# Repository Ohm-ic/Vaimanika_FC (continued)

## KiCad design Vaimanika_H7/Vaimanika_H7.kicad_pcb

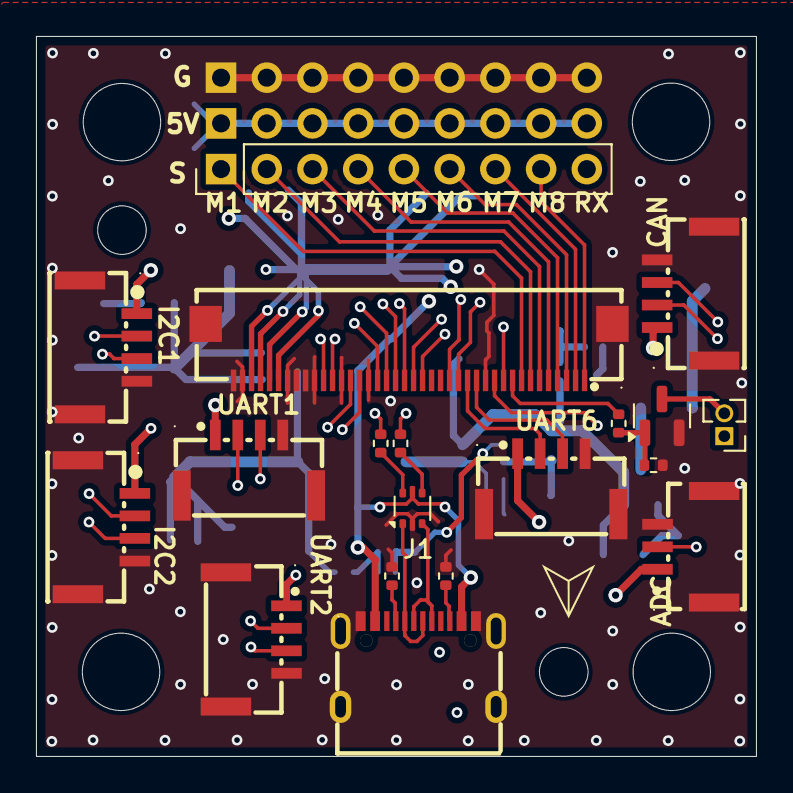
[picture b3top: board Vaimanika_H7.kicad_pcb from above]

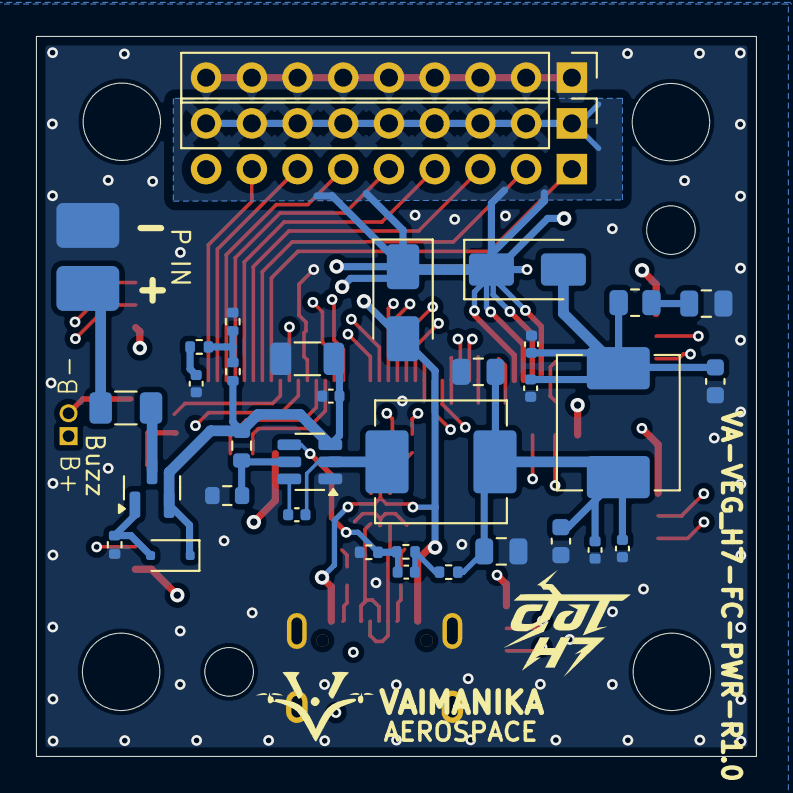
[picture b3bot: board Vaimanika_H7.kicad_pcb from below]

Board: 4 copper layers, 40.0 x 40.0 mm, 61 parts (36 on the bottom side), 50 nets.

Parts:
C2: 10uF; C_1206_3216Metric
C3, C16, C20: 100nF; C_0402_1005Metric
C5, C7: 0.1uF; C_0402_1005Metric
C9, C11: 22uF; C_0805_2012Metric
C12, C18: 4.7uF; C_0603_1608Metric
C14: 75pF; C_0402_1005Metric
C15, C19: 1uF; C_0402_1005Metric
C17: 47uF; C_0805_2012Metric
CN1: WAFER-GH1.25-3PWB; CONN-TH_3P-P1.25_GH1.25
D1, D2: SS34; D_SMA
D3: MM3Z10VT1G; D_SOD-323F
F1: CFS12V3T5R0; Fuse_1206_3216Metric
FPC1: AFC24-S40FIA-HF; FPC-SMD_40P-P0.50_AFC24-S40FIA-HF
H1, H2, H3, H4: MountingHole; MountingHole_4.3mm_M4
H5: MountingHole; MountingHole_2.7mm_M2.5_DIN965
H6: MountingHole; MountingHole_2.7mm_M2.5
J1: TYPE-C 16PIN 2MD; USB-C-SMD_TYPE-C-16PIN-2MD-073
J2, J3, J6: Conn_01x09; PinHeader_1x09_P2.54mm_Vertical
J4: +VLIPO; SolderPads_1x1_2.5_3.5
J5: GND; SolderPads_1x1_2.5_3.5
J8: Conn_01x02; PinHeader_1x02_P1.27mm_Vertical
L2: 10uH; L_TechFuse_SL0630
L3: 10uH; L_Chilisin_BMRB00060612
Q1: AO3400A; SOT-23
Q2: AO3401A; SOT-23
R1: 18K; R_0402_1005Metric
R2: 2K; R_0402_1005Metric
R3, R4: 100; R_0402_1005Metric
R5: 10K; R_0402_1005Metric
R8: 511K; R_0603_1608Metric
R9: 105K; R_0603_1608Metric
R10, R11: 22; R_0402_1005Metric
R12, R13: 5.1K; R_0402_1005Metric
R17: 49.9; R_0402_1005Metric
R18, R21: 100K; R_0402_1005Metric
R19: 13.3K; R_0402_1005Metric
R20: 1; R_0805_2012Metric
U2: TPS54302; SOT-23-6
U3: USBLC6-2P6; SOT-666
U4, U5, U6: WAFER-GH1.25-4PWB; CONN-SMD_4P-P1.25_XUNPU_WAFER-GH1.25-4PWB
U7, U8, U9: WAFER-GH1.25-4PLB; CONN-SMD_4P-P1.25_XUNPU_WAFER-GH1.25-4PLB

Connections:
+5VBAT: C9.1, C11.1, C12.1, C15.1, C16.1, L2.2, L3.1, R17.2
+5VBUS: D2.2 (A), J1.A4B9 (VBUS), J1.B4A9 (VBUS), U3.5 (VBUS)
+5VFIL: C18.1, C19.1, C20.1, D1.2 (A), L3.2, R20.2
+VIN: C2.1, C5.1, D3.1 (K), Q2.2 (S), R1.1, R8.2, U2.3 (VIN)
+VLIPO: F1.1, J4.1
ADC: CN1.2, FPC1.11
ADC_VOLTAGE: C3.1, R4.2
BUZZER: FPC1.9, R3.1
CAN_H: FPC1.27, U6.2
CAN_L: FPC1.26, U6.3
GND: C2.2, C3.2, C5.2, C9.2, C11.2, C12.2, C15.2, C16.2, C17.2, C18.2, C19.2, C20.2, CN1.3, CN1.4, CN1.5, FPC1.12, FPC1.25, FPC1.28, FPC1.31, FPC1.32, FPC1.33, FPC1.34, FPC1.39, FPC1.40, FPC1.41, FPC1.42, J1.13 (EH), J1.14 (EH), J1.A1B12 (GND), J1.B1A12 (GND), J3.1, J3.2, J3.3, J3.4, J3.5, J3.6, J3.7, J3.8, J3.9, J5.1, Q1.2 (S), R2.2, R5.2, R9.1, R12.1, R13.1, R19.1, R21.2, U2.1 (GND), U3.2 (GND), U4.4, U4.5, U4.6, U5.4, U5.5, U5.6, U6.4, U6.5, U6.6, U7.4, U7.5, U7.6, U8.4, U8.5, U8.6, U9.4, U9.5, U9.6
I2C2_SCL: FPC1.22, U5.2
I2C2_SDA: FPC1.21, U5.3
MOTOR1: FPC1.8, J6.1
MOTOR2: FPC1.7, J6.2
MOTOR3: FPC1.6, J6.3
MOTOR4: FPC1.5, J6.4
MOTOR5: FPC1.4, J6.5
MOTOR6: FPC1.3, J6.6
MOTOR7: FPC1.2, J6.7
MOTOR8: FPC1.1, J6.8
unnamed: C14.1, R17.1, R18.2
unnamed: C17.1, R20.1
unnamed: D3.2 (A), Q2.1 (G), R21.1
unnamed: J1.A5 (CC1), R12.2
unnamed: J1.B5 (CC2), R13.2
unnamed: Q1.1 (G), R3.2, R5.1
unnamed: F1.2, Q2.3 (D)
unnamed: R1.2, R2.1, R4.1
unnamed: R10.1, U3.6 (I/O1)
unnamed: R11.1, U3.4 (I/O2)
unnamed: C7.1, U2.6 (BOOT)
unnamed: R8.1, R9.2, U2.5 (EN)
unnamed: C14.2, R18.1, R19.2, U2.4 (FB)
unnamed: C7.2, L2.1, U2.2 (SW)
PIN_B+: CN1.1, D1.1 (K), D2.1 (K), FPC1.35, FPC1.36, FPC1.37, FPC1.38, J2.1, J2.2, J2.3, J2.4, J2.5, J2.6, J2.7, J2.8, J2.9, J8.1, U4.1, U5.1, U6.1, U7.1, U8.1, U9.1
PIN_B-: J8.2, Q1.3 (D)
RX_PPM: FPC1.10, J6.9
SCL_BARO: FPC1.23, U4.2
SDA_BARO: FPC1.24, U4.3
UART2_RX: FPC1.15, U8.3
UART2_TX: FPC1.16, U8.2
USART1_RX: FPC1.19, U9.3
USART1_TX: FPC1.20, U9.2
USART6_RX: FPC1.13, U7.3
USART6_TX: FPC1.14, U7.2
USB_CON_D+: J1.A6 (Dp1), J1.B6 (Dp2), U3.3 (I/O2)
USB_CON_D-: J1.A7 (Dn1), J1.B7 (Dn2), U3.1 (I/O1)
USB_D+: FPC1.30, R11.2
USB_D-: FPC1.29, R10.2

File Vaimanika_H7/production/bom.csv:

Designator,Footprint,Quantity,Value,LCSC Part #
"C11, C9",0805,2,22uF,C6119899
"C12, C18",0603,2,4.7uF,C19666
C14,0402,1,75pF,C107010
"C15, C19",0402,2,1uF,C14445
"C16, C20, C3",0402,3,100nF,C60474
C17,0805,1,47uF,C16780
C2,1206,1,10uF,C7432781
"C5, C7",0402,2,0.1uF,C152814
CN1,CONN-TH_3P-P1.25_GH1.25,1,WAFER-GH1.25-3PWB,C3029378
"D1, D2",D_SMA,2,SS34,C8678
D3,D_SOD-323F,1,MM3Z10VT1G,C39057
F1,1206,1,CFS12V3T5R0,C163128
FPC1,FPC-SMD_40P-P0.50_AFC24-S40FIA-HF,1,AFC24-S40FIA-HF,C49260550
J1,USB-C-SMD_TYPE-C-16PIN-2MD-073,1,TYPE-C 16PIN 2MD,C2765186
"J2, J3, J6",PinHeader_1x09_P2.54mm_Vertical,3,Conn_01x09,
J4,SolderPads_1x1_2.5_3.5,1,+VLIPO,
J5,SolderPads_1x1_2.5_3.5,1,GND,
J8,PinHeader_1x02_P1.27mm_Vertical,1,Conn_01x02,
L2,L_TechFuse_SL0630,1,10uH,C917354
L3,L_Chilisin_BMRB00060612,1,10uH,C128692
Q1,SOT-23,1,AO3400A,C20917
Q2,SOT-23,1,AO3401A,C15127
R1,0402,1,18K,C25762
"R10, R11",0402,2,22,C114765
"R12, R13",0402,2,5.1K,C25905
R17,0402,1,49.9,C87044
"R18, R21",0402,2,100K,C60491
R19,0402,1,13.3K,C2974007
R2,0402,1,2K,C4109
R20,0805,1,1,C2907233
"R3, R4",0402,2,100,C106232
R5,0402,1,10K,C25744
R8,0603,1,511K,C2930114
R9,0603,1,105K,C2933128
U2,SOT-23-6,1,TPS54302,C311983
U3,SOT-666,1,USBLC6-2P6,C15999
"U4, U5, U6",CONN-SMD_4P-P1.25_XUNPU_WAFER-GH1.25-4PWB,3,WAFER-GH1.25-4PWB,C3029379
"U7, U8, U9",CONN-SMD_4P-P1.25_XUNPU_WAFER-GH1.25-4PLB,3,WAFER-GH1.25-4PLB,C3029370

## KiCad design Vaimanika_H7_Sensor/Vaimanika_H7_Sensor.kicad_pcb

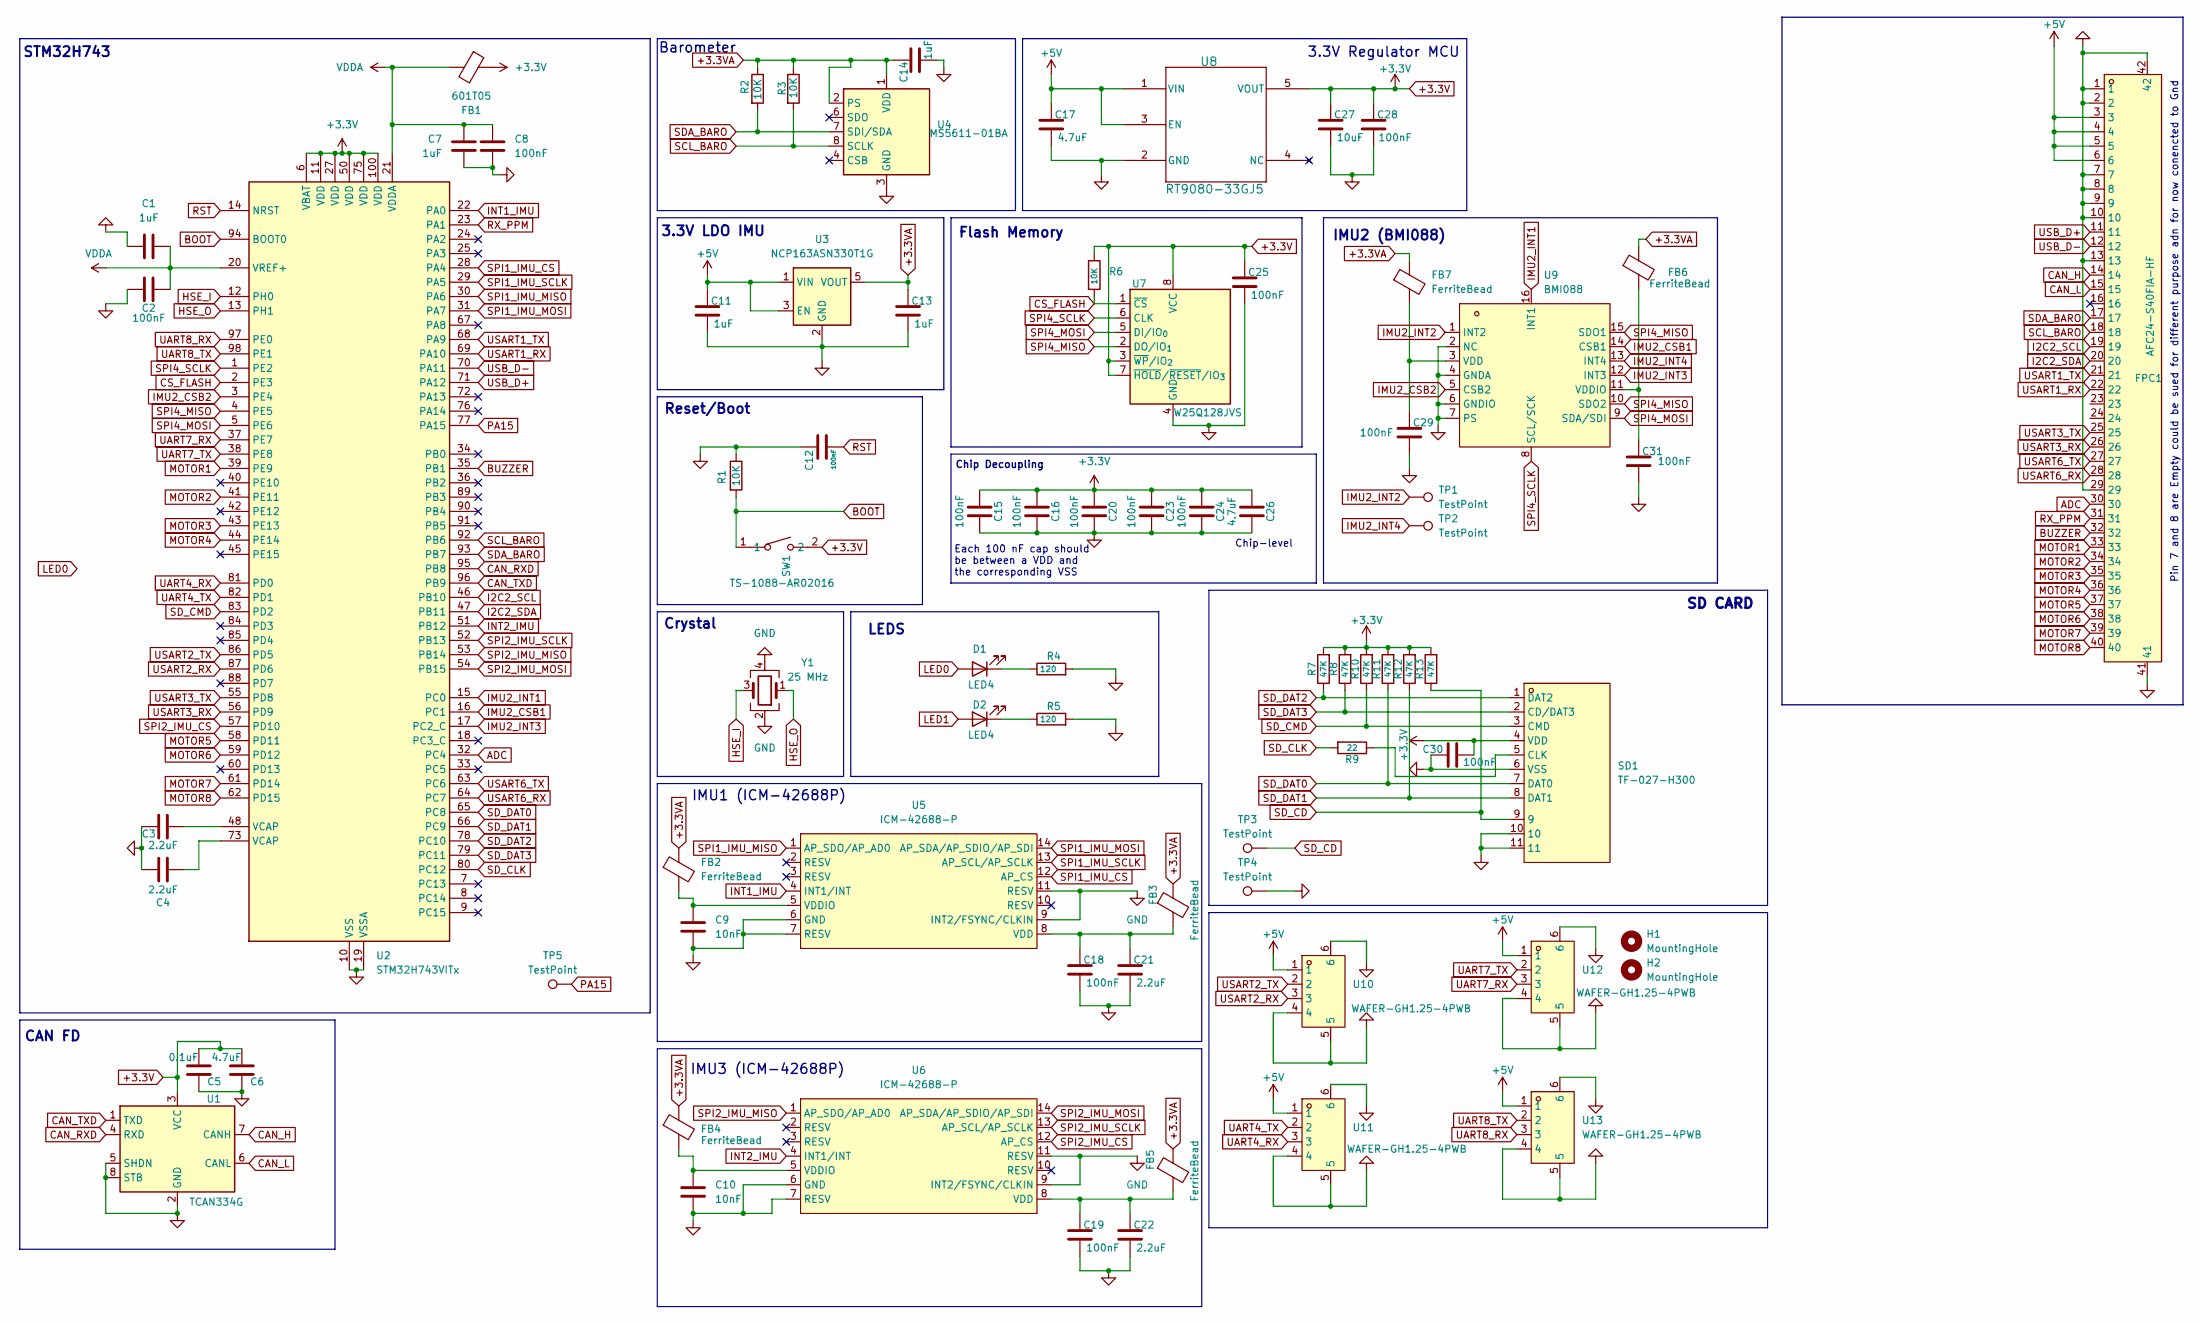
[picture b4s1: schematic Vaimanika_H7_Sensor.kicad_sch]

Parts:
C1, C7, C11, C13, C14: 1uF; C_0402_1005Metric; LCSC C380294
C2, C8, C12, C15, C16, C18, C19, C20, C23, C24, C25, C28, C29, C30, C31: 100nF; C_0402_1005Metric; LCSC C60474
C3, C4, C21, C22: 2.2uF; C_0402_1005Metric; LCSC C53032641
C5: 0.1uF; C_0402_1005Metric; LCSC C152814
C6, C17, C26: 4.7uF; C_0402_1005Metric; LCSC C6119782
C9, C10: 10nF; C_0402_1005Metric; LCSC C6119808
C27: 10uF; C_0402_1005Metric; LCSC C15525
D1, D2: LED4; LED_0402_1005Metric; LCSC C965793
FB1: 601T05; L_0603_1608Metric; LCSC C133937
FB2, FB3, FB4, FB5, FB6, FB7: FerriteBead; L_0402_1005Metric; LCSC C76884
FPC1: AFC24-S40FIA-HF; FPC-SMD_40P-P0.50_AFC24-S40FIA-HF; MPN AFC24-S40FIA-HF; LCSC Part C49260550
H1, H2: MountingHole; MountingHole_2.7mm_M2.5_DIN965
R1, R6: 10K; R_0402_1005Metric; LCSC C25744
R2, R3: 10K; C_0402_1005Metric; LCSC C25744
R4, R5: 120; R_0402_1005Metric; LCSC C25079
R7, R8, R10, R11, R12, R13: 47K; R_0402_1005Metric; LCSC C25133
R9: 22; R_0402_1005Metric; LCSC C114765
SD1: TF-027-H300; TF-SMD_HYCW104-TF08-375B; LCSC Part C5310495
SW1: TS-1088-AR02016; SW-SMD_L3.9-W3.0-P4.45; LCSC C720477
TP1, TP2, TP3, TP4, TP5: TestPoint; TestPoint_Pad_D1.0mm
U1: TCAN334G; SOT-23-8; LCSC C191005
U2: STM32H743VITx; LQFP-100_14x14mm_P0.5mm; LCSC C114409
U3: NCP163ASN330T1G; SOT-23-5; LCSC C892187
U4: MS5611-01BA; LGA-8_3x5mm_P1.25mm; LCSC C15639
U5, U6: ICM-42688-P; LGA-14_L3.0-W2.5-P0.50-TL; LCSC Part C1850418
U7: W25Q128JVS; SOIC-8_L5.3-W5.3-P1.27-LS8.0-BL; LCSC C97521
U8: RT9080-33GJ5; TSOT-23-5; LCSC C841192
U9: BMI088; LGA-16_L4.5-W3.0-P0.50-BL; LCSC Part C194919
U10, U11, U12, U13: WAFER-GH1.25-4PWB; CONN-SMD_4P-P1.25_XUNPU_WAFER-GH1.25-4PWB; MPN WAFER-GH1.25-4PWB; LCSC C3029379
Y1: 25 MHz; CRYSTAL-SMD_4P-L3.2-W2.5-BL; LCSC C3034302

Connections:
+3.3V: C5.2, C6.2, C15.1, C16.1, C20.1, C23.1, C24.1, C25.1, C26.1, C27.1, C28.1, C30.2, FB1.1, R6.1, R7.2, R8.2, R10.2, R11.2, R12.2, R13.2, SD1.4 (VDD), SW1.2, U1.3 (VCC), U2.6 (VBAT), U2.11 (VDD), U2.27 (VDD), U2.50 (VDD), U2.75 (VDD), U2.100 (VDD), U7.3 (~WP/IO_{2}), U7.7 (~HOLD/~RESET/IO_{3}), U7.8 (VCC), U8.5 (VOUT)
+3.3VA: C13.1, C14.1, FB2.1, FB3.1, FB4.1, FB5.1, FB6.1, FB7.1, R2.1, R3.1, U3.5 (VOUT), U4.1 (VDD), U4.2 (PS)
+5V: C11.1, C17.1, FPC1.3, FPC1.4, FPC1.5, FPC1.6, U3.1 (VIN), U3.3 (EN), U8.1 (VIN), U8.3 (EN), U10.1, U11.1, U12.1, U13.1
ADC: FPC1.30, U2.32 (PC4)
BOOT: R1.2, SW1.1, U2.94 (BOOT0)
BUZZER: FPC1.32, U2.35 (PB1)
CAN_H: FPC1.14, U1.7 (CANH)
CAN_L: FPC1.15, U1.6 (CANL)
CAN_RXD: U1.4 (RXD), U2.95 (PB8)
CAN_TXD: U1.1 (TXD), U2.96 (PB9)
CS_FLASH: R6.2, U2.2 (PE3), U7.1 (~CS)
GND: C1.1, C2.1, C3.1, C4.1, C5.1, C6.1, C7.2, C8.2, C9.2, C10.2, C11.2, C12.1, C13.2, C14.2, C15.2, C16.2, C17.2, C18.2, C19.2, C20.2, C21.2, C22.2, C23.2, C24.2, C25.2, C26.2, C27.2, C28.2, C29.2, C30.1, C31.2, FPC1.1, FPC1.2, FPC1.7, FPC1.8, FPC1.9, FPC1.10, FPC1.13, FPC1.29, FPC1.41, FPC1.42, R1.1, R4.2, R5.2, SD1.6 (VSS), SD1.10, SD1.11, TP4.1, U1.2 (GND), U1.5 (SHDN), U1.8 (STB), U2.10 (VSS), U2.19 (VSSA), U2.26 (VSS), U2.49 (VSS), U2.74 (VSS), U2.99 (VSS), U3.2 (GND), U4.3 (GND), U5.6 (GND), U5.7 (RESV), U5.9 (INT2/FSYNC/CLKIN), U5.11 (RESV), U6.6 (GND), U6.7 (RESV), U6.9 (INT2/FSYNC/CLKIN), U6.11 (RESV), U7.4 (GND), U8.2 (GND), U9.2 (NC), U9.4 (GNDA), U9.6 (GNDIO), U9.7 (PS), U10.4, U10.5, U10.6, U11.4, U11.5, U11.6, U12.4, U12.5, U12.6, U13.4, U13.5, U13.6, Y1.2, Y1.4
HSE_I: U2.12 (PH0), Y1.3
HSE_O: U2.13 (PH1), Y1.1
I2C2_SCL: FPC1.19, U2.46 (PB10)
I2C2_SDA: FPC1.20, U2.47 (PB11)
IMU2_CSB1: U2.16 (PC1), U9.14 (CSB1)
IMU2_CSB2: U2.3 (PE4), U9.5 (CSB2)
IMU2_INT1: U2.15 (PC0), U9.16 (INT1)
IMU2_INT2: TP1.1, U9.1 (INT2)
IMU2_INT3: U2.17 (PC2_C), U9.12 (INT3)
IMU2_INT4: TP2.1, U9.13 (INT4)
INT1_IMU: U2.22 (PA0), U5.4 (INT1/INT)
INT2_IMU: U2.51 (PB12), U6.4 (INT1/INT)
LED0: D1.2 (A)
LED1: D2.2 (A)
MOTOR1: FPC1.33, U2.39 (PE9)
MOTOR2: FPC1.34, U2.41 (PE11)
MOTOR3: FPC1.35, U2.43 (PE13)
MOTOR4: FPC1.36, U2.44 (PE14)
MOTOR5: FPC1.37, U2.58 (PD11)
MOTOR6: FPC1.38, U2.59 (PD12)
MOTOR7: FPC1.39, U2.61 (PD14)
MOTOR8: FPC1.40, U2.62 (PD15)
unnamed: C3.2, U2.48 (VCAP)
unnamed: C4.2, U2.73 (VCAP)
unnamed: D1.1 (K), R4.1
unnamed: D2.1 (K), R5.1
unnamed: R9.1, SD1.5 (CLK)
unnamed: C18.1, C21.1, FB3.2, U5.8 (VDD)
unnamed: C9.1, FB2.2, U5.5 (VDDIO)
unnamed: C19.1, C22.1, FB5.2, U6.8 (VDD)
unnamed: C10.1, FB4.2, U6.5 (VDDIO)
unnamed: C29.1, FB7.2, U9.3 (VDD)
unnamed: C31.1, FB6.2, U9.11 (VDDIO)
PA15: TP5.1, U2.77 (PA15)
RST: C12.2, U2.14 (NRST)
RX_PPM: FPC1.31, U2.23 (PA1)
SCL_BARO: FPC1.18, R3.2, U2.92 (PB6), U4.8 (SCLK)
SDA_BARO: FPC1.17, R2.2, U2.93 (PB7), U4.7 (SDI/SDA)
SD_CD: R13.1, SD1.9, TP3.1
SD_CLK: R9.2, U2.80 (PC12)
SD_CMD: R10.1, SD1.3 (CMD), U2.83 (PD2)
SD_DAT0: R11.1, SD1.7 (DAT0), U2.65 (PC8)
SD_DAT1: R12.1, SD1.8 (DAT1), U2.66 (PC9)
SD_DAT2: R7.1, SD1.1 (DAT2), U2.78 (PC10)
SD_DAT3: R8.1, SD1.2 (CD/DAT3), U2.79 (PC11)
SPI1_IMU_CS: U2.28 (PA4), U5.12 (AP_CS)
SPI1_IMU_MISO: U2.30 (PA6), U5.1 (AP_SDO/AP_AD0)
SPI1_IMU_MOSI: U2.31 (PA7), U5.14 (AP_SDA/AP_SDIO/AP_SDI)
SPI1_IMU_SCLK: U2.29 (PA5), U5.13 (AP_SCL/AP_SCLK)
SPI2_IMU_CS: U2.57 (PD10), U6.12 (AP_CS)
SPI2_IMU_MISO: U2.53 (PB14), U6.1 (AP_SDO/AP_AD0)
SPI2_IMU_MOSI: U2.54 (PB15), U6.14 (AP_SDA/AP_SDIO/AP_SDI)
SPI2_IMU_SCLK: U2.52 (PB13), U6.13 (AP_SCL/AP_SCLK)
SPI4_MISO: U2.4 (PE5), U7.2 (DO/IO_{1}), U9.10 (SDO2), U9.15 (SDO1)
SPI4_MOSI: U2.5 (PE6), U7.5 (DI/IO_{0}), U9.9 (SDA/SDI)
SPI4_SCLK: U2.1 (PE2), U7.6 (CLK), U9.8 (SCL/SCK)
UART4_RX: U2.81 (PD0), U11.3
UART4_TX: U2.82 (PD1), U11.2
UART7_RX: U2.37 (PE7), U12.3
UART7_TX: U2.38 (PE8), U12.2
UART8_RX: U2.97 (PE0), U13.3
UART8_TX: U2.98 (PE1), U13.2
USART1_RX: FPC1.22, U2.69 (PA10)
USART1_TX: FPC1.21, U2.68 (PA9)
USART2_RX: U2.87 (PD6), U10.3
USART2_TX: U2.86 (PD5), U10.2
USART3_RX: FPC1.26, U2.56 (PD9)
USART3_TX: FPC1.25, U2.55 (PD8)
USART6_RX: FPC1.28, U2.64 (PC7)
USART6_TX: FPC1.27, U2.63 (PC6)
USB_D+: FPC1.11, U2.71 (PA12)
USB_D-: FPC1.12, U2.70 (PA11)
VDDA: C1.2, C2.2, C7.1, C8.1, FB1.2, U2.20 (VREF+), U2.21 (VDDA)

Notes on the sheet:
CAN FD
Flash Memory
Chip Decoupling
SD CARD
LEDS
Crystal
3.3V LDO IMU
Each 100 nF cap should be between a VDD and the corresponding VSS
Barometer
3.3V Regulator MCU
Pin 7 and 8 are Empty could be sued for different purpose adn for now conencted to Gnd
IMU1 (ICM-42688P)
IMU2 (BMI088)
STM32H743
IMU3 (ICM-42688P)
Reset/Boot
Chip-level

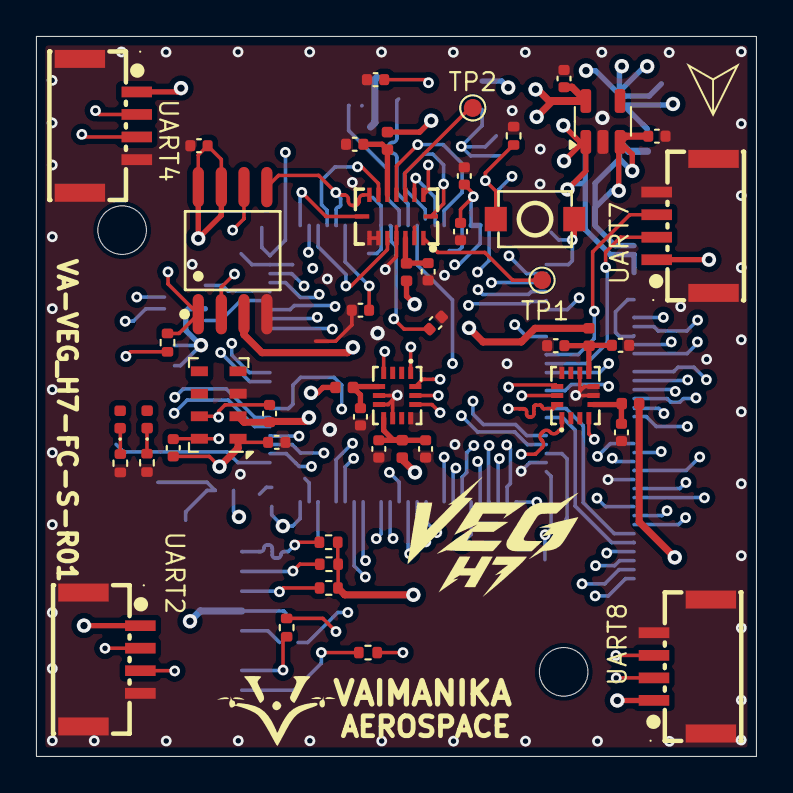
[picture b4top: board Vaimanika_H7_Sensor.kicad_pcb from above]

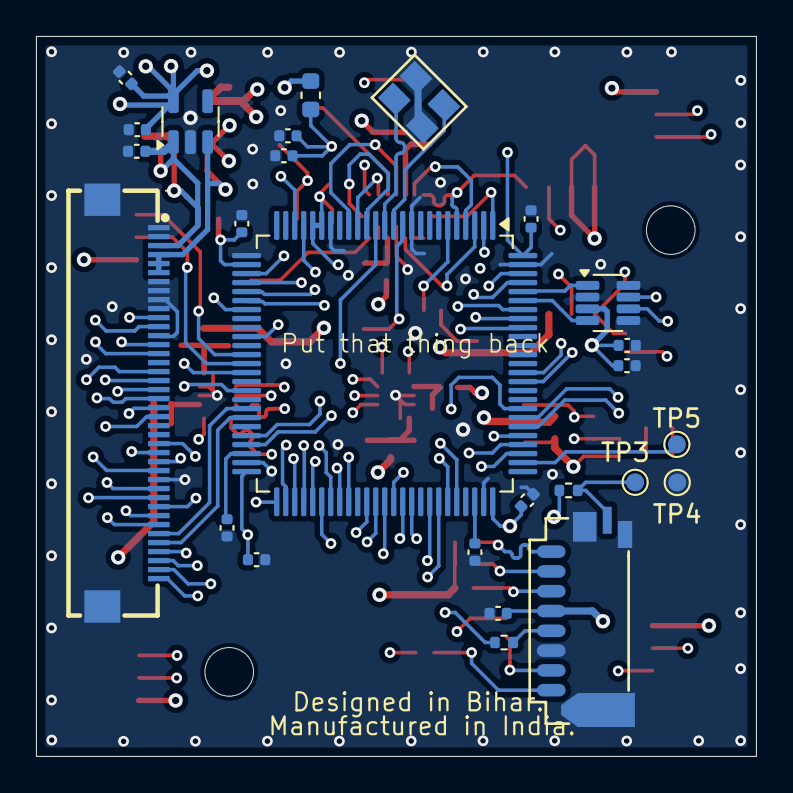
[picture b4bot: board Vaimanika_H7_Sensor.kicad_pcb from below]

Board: 8 copper layers, 40.0 x 40.0 mm, 77 parts (26 on the bottom side), 83 nets.

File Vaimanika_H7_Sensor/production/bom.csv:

Designator,Footprint,Quantity,Value,LCSC Part #
"C1, C11, C13, C14, C7",0402,5,1uF,C380294
"C10, C9",0402,2,10nF,C6119808
"C12, C15, C16, C18, C19, C2, C20, C23, C24, C25, C28, C29, C30, C31, C8",0402,15,100nF,C60474
"C17, C26, C6",0402,3,4.7uF,C6119782
"C21, C22, C3, C4",0402,4,2.2uF,C53032641
C27,0402,1,10uF,C15525
C5,0402,1,0.1uF,C152814
"D1, D2",0402,2,LED4,C965793
FB1,0603,1,601T05,C133937
"FB2, FB3, FB4, FB5, FB6, FB7",0402,6,FerriteBead,C76884
FPC1,FPC-SMD_40P-P0.50_AFC24-S40FIA-HF,1,AFC24-S40FIA-HF,C49260550
"R1, R2, R3, R6",0402,4,10K,C25744
"R10, R11, R12, R13, R7, R8",0402,6,47K,C25133
"R4, R5",0402,2,120,C25079
R9,0402,1,22,C114765
SD1,TF-SMD_HYCW104-TF08-375B,1,TF-027-H300,C5310495
SW1,SW-SMD_L3.9-W3.0-P4.45,1,TS-1088-AR02016,C720477
"TP1, TP2, TP3, TP4, TP5",TestPoint_Pad_D1.0mm,5,TestPoint,
U1,SOT-23-8,1,TCAN334G,C191005
"U10, U11, U12, U13",CONN-SMD_4P-P1.25_XUNPU_WAFER-GH1.25-4PWB,4,WAFER-GH1.25-4PWB,C3029379
U2,LQFP-100_14x14mm_P0.5mm,1,STM32H743VITx,C114409
U3,SOT-23-5,1,NCP163ASN330T1G,C892187
U4,LGA-8_3x5mm_P1.25mm,1,MS5611-01BA,C15639
"U5, U6",LGA-14_L3.0-W2.5-P0.50-TL,2,ICM-42688-P,C1850418
U7,SOIC-8_L5.3-W5.3-P1.27-LS8.0-BL,1,W25Q128JVS,C97521
U8,TSOT-23-5,1,RT9080-33GJ5,C841192
U9,LGA-16_L4.5-W3.0-P0.50-BL,1,BMI088,C194919
Y1,CRYSTAL-SMD_4P-L3.2-W2.5-BL,1,25 MHz,C3034302

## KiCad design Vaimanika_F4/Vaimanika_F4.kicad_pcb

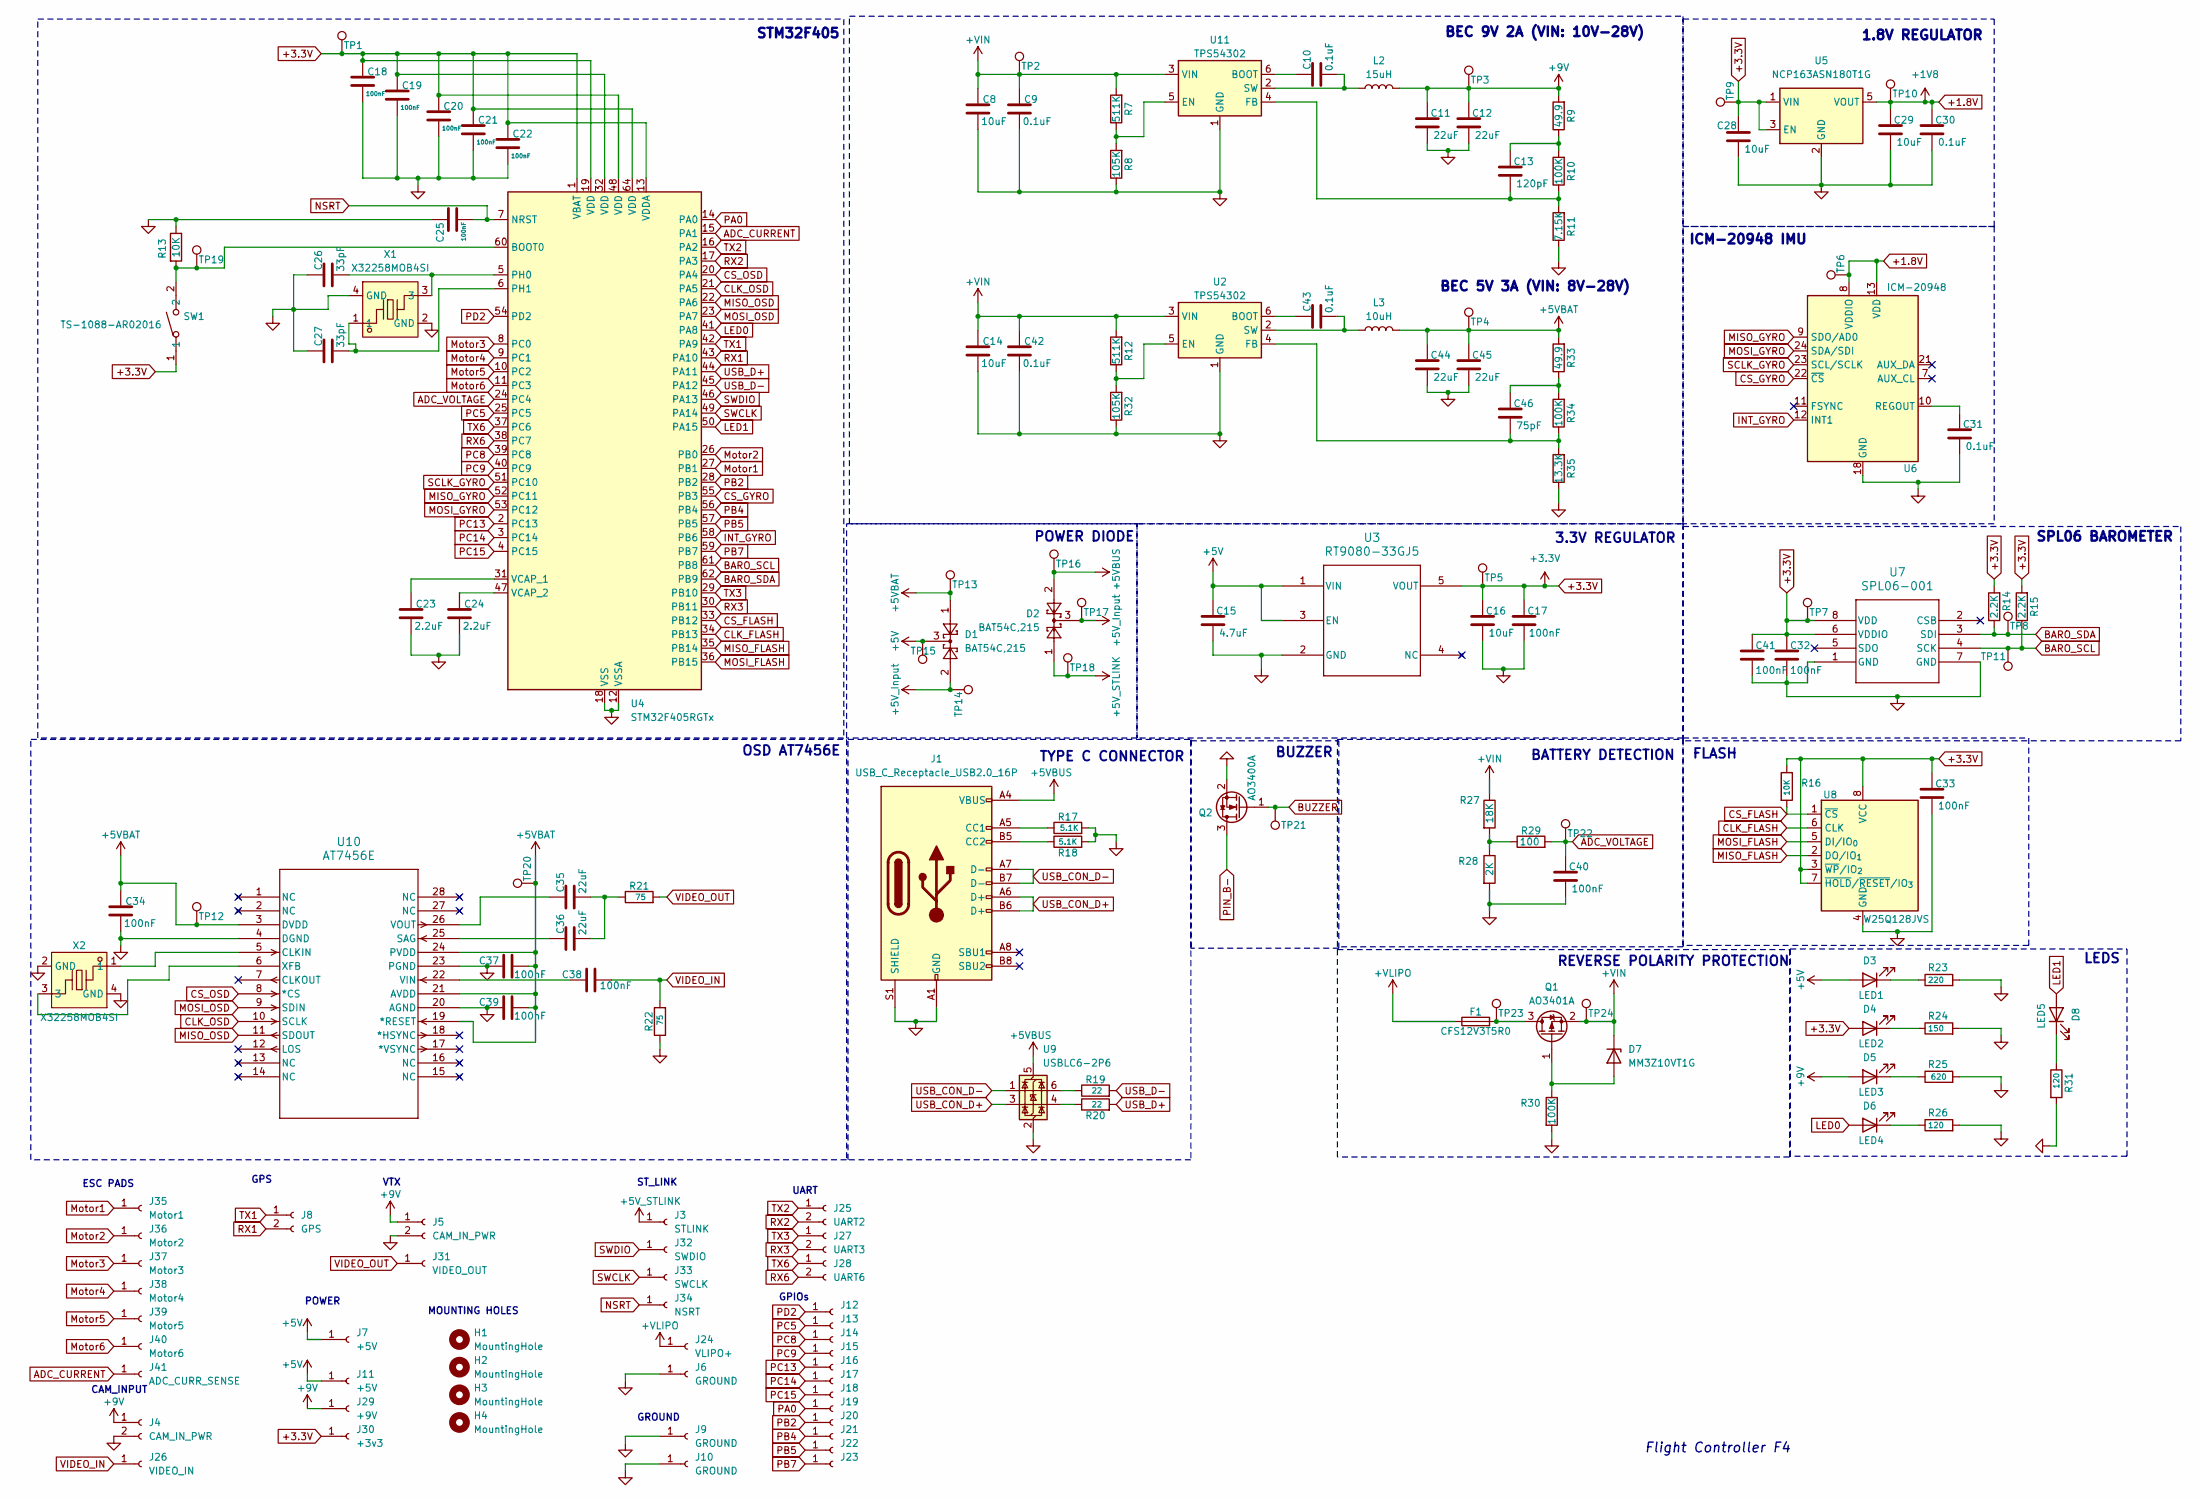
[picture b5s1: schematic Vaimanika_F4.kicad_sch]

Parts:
C8, C14: 10uF; C_1206_3216Metric; LCSC C7432781
C9, C10, C30, C31, C42, C43: 0.1uF; C_0402_1005Metric; LCSC C152814
C11, C12, C35, C36, C44, C45: 22uF; C_0603_1608Metric; LCSC C6119863
C13: 120pF; C_0402_1005Metric; LCSC C541468
C15: 4.7uF; C_0402_1005Metric; LCSC C6119782
C16, C28, C29: 10uF; C_0402_1005Metric; LCSC C15525
C17, C18, C19, C20, C21, C22, C25, C32, C33, C34, C37, C38, C39, C40, C41: 100nF; C_0402_1005Metric; LCSC C60474
C23, C24: 2.2uF; C_0402_1005Metric; LCSC C20539421
C26, C27: 33pF; C_0402_1005Metric; LCSC C326803
C46: 75pF; C_0402_1005Metric; LCSC C107010
D1, D2: BAT54C,215; SOT-323_SC-70; LCSC C916424
D3: LED1; LED_0402_1005Metric; LCSC C25503345
D4: LED2; LED_0402_1005Metric; LCSC C25503345
D5: LED3; LED_0402_1005Metric; LCSC C25503345
D6: LED4; LED_0402_1005Metric; LCSC C965793
D7: MM3Z10VT1G; D_SOD-323F; LCSC C39057
D8: LED5; LED_0402_1005Metric; LCSC C965791
F1: CFS12V3T5R0; Fuse_1206_3216Metric; LCSC C163128
H1, H2, H3, H4: MountingHole; MountingHole_4.3mm_M4_ISO14580
J1: USB_C_Receptacle_USB2.0_16P; USB_C_Receptacle_GCT_USB4105-xx-A_16P_TopMnt_Horizontal; LCSC C2765186
J3: STLINK; SolderPads_1x1
J4, J5: CAM_IN_PWR; SolderPads_1x2
J6: GROUND; SolderPads_1x1_2.5_3.5; LCSC N/A
J7: +5V; SolderPads_1x1
J8: GPS; SolderPads_1x2
J9, J10: GROUND; SolderPads_1x1; LCSC N/A
J11: +5V
J12, J13, J14, J15, J16, J17, J18, J19, J20, J21, J22, J23: Conn_01x01_Socket; SolderPads_1x1; LCSC N/A
J24: VLIPO+; SolderPads_1x1_2.5_3.5
J25: UART2; SolderPads_1x2
J26: VIDEO_IN; SolderPads_1x1
J27: UART3; SolderPads_1x2
J28: UART6; SolderPads_1x2
J29: +9V; SolderPads_1x1
J30: +3v3; SolderPads_1x1
J31: VIDEO_OUT; SolderPads_1x1
J32: SWDIO; SolderPads_1x1
J33: SWCLK; SolderPads_1x1
J34: NSRT; SolderPads_1x1
J35: Motor1; SolderPads_1x1
J36: Motor2; SolderPads_1x1
J37: Motor3; SolderPads_1x1
J38: Motor4; SolderPads_1x1
J39: Motor5; SolderPads_1x1
J40: Motor6; SolderPads_1x1
J41: ADC_CURR_SENSE; SolderPads_1x1
L2: 15uH; L_TechFuse_SL0630; LCSC C5349699
L3: 10uH; L_TechFuse_SL0630; LCSC C917354
Q1: AO3401A; SOT-23; LCSC C15127
Q2: AO3400A; SOT-23; LCSC C20917
R7, R12: 511K; R_0603_1608Metric; LCSC C2930114
R8, R32: 105K; R_0603_1608Metric; LCSC C2933128
R9, R33: 49.9; R_0402_1005Metric; LCSC C2909367
R10, R30, R34: 100K; R_0402_1005Metric; LCSC C60491
R11: 7.15K; R_0402_1005Metric; LCSC C2909367
R13, R16: 10K; R_0402_1005Metric; LCSC C25744
R14, R15: 2.2K; R_0402_1005Metric; LCSC C25879
R17, R18: 5.1K; R_0402_1005Metric; LCSC C25905
R19, R20: 22; R_0402_1005Metric; LCSC C114765
R21, R22: 75; R_0402_1005Metric; LCSC C25133
R23: 220; R_0402_1005Metric; LCSC C25091
R24: 150; R_0402_1005Metric; LCSC C138054
R25: 620; R_0402_1005Metric; LCSC C4961
R26, R31: 120; R_0402_1005Metric; LCSC C25079
R27: 18K; R_0402_1005Metric; LCSC C25762
R28: 2K; R_0402_1005Metric; LCSC C4109
R29: 100; R_0402_1005Metric; LCSC C106232
R35: 13.3K; R_0402_1005Metric; LCSC C2909367
SW1: TS-1088-AR02016; SW-SMD_L3.9-W3.0-P4.45; LCSC C720477
TP1, TP2, TP3, TP4, TP5, TP6, TP7, TP8, TP9, TP10, TP11, TP12, TP13, TP14, TP15, TP16, TP17, TP18, TP19, TP20, TP21, TP22, TP23, TP24: TestPoint; TestPoint_Pad_D1.0mm; LCSC N/A
U2, U11: TPS54302; SOT-23-6; LCSC C311983
U3: RT9080-33GJ5; TSOT-23-5; LCSC C841192
U4: STM32F405RGTx; LQFP-64_10x10mm_P0.5mm; LCSC C15742
U5: NCP163ASN180T1G; SOT-23-5; LCSC C892206
U6: ICM-20948; InvenSense_QFN-24_3x3mm_P0.4mm; LCSC C726001
U7: SPL06-001; SENSOR-SMD_SPL06-001; LCSC C2684428
U8: W25Q128JVS; SOIC-8_L5.3-W5.3-P1.27-LS8.0-BL; LCSC C97521
U9: USBLC6-2P6; SOT-666; LCSC C15999
U10: AT7456E; TSSOP-28-1EP_4.4x9.7mm_P0.65mm_EP2.74x4.75mm; LCSC C82351
X1, X2: X32258MOB4SI; CRYSTAL-SMD_4P-L3.2-W2.5-BL; LCSC Part C2682775

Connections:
+1.8V: C29.1, C30.1, TP6.1, TP10.1, U5.5 (VOUT), U6.8 (VDDIO), U6.13 (VDD)
+3.3V: C16.1, C17.1, C18.1, C19.1, C20.1, C21.1, C22.1, C28.1, C32.1, C33.1, C41.1, D4.2 (A), J30.1, R14.2, R15.2, R16.1, SW1.1, TP1.1, TP5.1, TP7.1, TP9.1, U3.5 (VOUT), U4.1 (VBAT), U4.13 (VDDA), U4.19 (VDD), U4.32 (VDD), U4.48 (VDD), U4.64 (VDD), U5.1 (VIN), U5.3 (EN), U7.6 (VDDIO), U7.8 (VDD), U8.3 (~WP/IO_{2}), U8.7 (~HOLD/~RESET/IO_{3}), U8.8 (VCC)
+5V: C15.1, D1.3, D3.2 (A), J7.1, J11.1, TP15.1, U3.1 (VIN), U3.3 (EN)
+5VBAT: C34.1, C37.2, C39.2, C44.1, C45.1, D1.1, L3.2, R33.2, TP4.1, TP12.1, TP13.1, TP20.1, U10.3 (DVDD), U10.19 (*RESET), U10.21 (AVDD), U10.24 (PVDD)
+5VBUS: D2.2, J1.A4 (VBUS), J1.A9 (VBUS), J1.B4 (VBUS), J1.B9 (VBUS), TP16.1, U9.5 (VBUS)
+5V_Input: D1.2, D2.3, TP14.1, TP17.1
+5V_STLINK: D2.1, J3.1, TP18.1
+9V: C11.1, C12.1, D5.2 (A), J4.1, J5.1, J29.1, L2.2, R9.2, TP3.1
+VIN: C8.1, C9.1, C14.1, C42.1, D7.1 (K), Q1.2 (S), R7.2, R12.2, R27.1, TP2.1, TP24.1, U2.3 (VIN), U11.3 (VIN)
+VLIPO: F1.1, J24.1
ADC_CURRENT: J41.1, U4.15 (PA1)
ADC_VOLTAGE: C40.1, R29.2, TP22.1, U4.24 (PC4)
BARO_SCL: R15.1, TP11.1, U4.61 (PB8), U7.4 (SCK)
BARO_SDA: R14.1, TP8.1, U4.62 (PB9), U7.3 (SDI)
BUZZER: Q2.1 (G), TP21.1
CLK_FLASH: U4.34 (PB13), U8.6 (CLK)
CLK_OSD: U4.21 (PA5), U10.10 (SCLK)
CS_FLASH: R16.2, U4.33 (PB12), U8.1 (~CS)
CS_GYRO: U4.55 (PB3), U6.22 (~CS)
CS_OSD: U4.20 (PA4), U10.8 (*CS)
GND: C8.2, C9.2, C11.2, C12.2, C14.2, C15.2, C16.2, C17.2, C18.2, C19.2, C20.2, C21.2, C22.2, C23.2, C24.2, C25.1, C26.1, C27.1, C28.2, C29.2, C30.2, C31.2, C32.2, C33.2, C34.2, C37.1, C39.1, C40.2, C41.2, C42.2, C44.2, C45.2, J1.A1 (GND), J1.A12 (GND), J1.B1 (GND), J1.B12 (GND), J1.S1 (SHIELD), J4.2, J5.2, J6.1, J9.1, J10.1, Q2.2 (S), R8.1, R11.1, R13.1, R17.2, R18.2, R22.1, R23.2, R24.2, R25.2, R26.2, R28.2, R30.2, R31.2, R32.1, R35.1, U2.1 (GND), U3.2 (GND), U4.12 (VSSA), U4.18 (VSS), U4.63 (VSS), U5.2 (GND), U6.18 (GND), U6.20 (GND), U7.1 (GND), U7.7 (GND), U8.4 (GND), U9.2 (GND), U10.4 (DGND), U10.20 (AGND), U10.23 (PGND), U11.1 (GND), X1.2 (GND), X1.4 (GND), X2.2 (GND), X2.4 (GND)
INT_GYRO: U4.58 (PB6), U6.12 (INT1)
LED0: D6.2 (A), U4.41 (PA8)
LED1: D8.2 (A), U4.50 (PA15)
MISO_FLASH: U4.35 (PB14), U8.2 (DO/IO_{1})
MISO_GYRO: U4.52 (PC11), U6.9 (SDO/AD0)
MISO_OSD: U4.22 (PA6), U10.11 (SDOUT)
MOSI_FLASH: U4.36 (PB15), U8.5 (DI/IO_{0})
MOSI_GYRO: U4.53 (PC12), U6.24 (SDA/SDI)
MOSI_OSD: U4.23 (PA7), U10.9 (SDIN)
Motor1: J35.1, U4.27 (PB1)
Motor2: J36.1, U4.26 (PB0)
Motor3: J37.1, U4.8 (PC0)
Motor4: J38.1, U4.9 (PC1)
Motor5: J39.1, U4.10 (PC2)
Motor6: J40.1, U4.11 (PC3)
NSRT: C25.2, J34.1, U4.7 (NRST)
unnamed: C13.1, R9.1, R10.2
unnamed: C35.2, C36.2, R21.1
unnamed: C46.1, R33.1, R34.2
unnamed: D3.1 (K), R23.1
unnamed: D4.1 (K), R24.1
unnamed: D5.1 (K), R25.1
unnamed: D6.1 (K), R26.1
unnamed: D7.2 (A), Q1.1 (G), R30.1
unnamed: D8.1 (K), R31.1
unnamed: J1.A5 (CC1), R17.1
unnamed: J1.B5 (CC2), R18.1
unnamed: F1.2, Q1.3 (D), TP23.1
unnamed: R19.1, U9.6 (I/O1)
unnamed: R20.1, U9.4 (I/O2)
unnamed: R27.2, R28.1, R29.1
unnamed: C43.1, U2.6 (BOOT)
unnamed: R12.1, R32.2, U2.5 (EN)
unnamed: C46.2, R34.1, R35.2, U2.4 (FB)
unnamed: C43.2, L3.1, U2.2 (SW)
unnamed: R13.2, SW1.2, TP19.1, U4.60 (BOOT0)
unnamed: C26.2, U4.5 (PH0), X1.3
unnamed: C27.2, U4.6 (PH1), X1.1
unnamed: C23.1, U4.31 (VCAP_1)
unnamed: C24.1, U4.47 (VCAP_2)
unnamed: C31.1, U6.10 (REGOUT)
unnamed: U10.5 (CLKIN), X2.1
unnamed: C36.1, U10.25 (SAG)
unnamed: C38.1, U10.22 (VIN)
unnamed: C35.1, U10.26 (VOUT)
unnamed: U10.6 (XFB), X2.3
unnamed: C10.1, U11.6 (BOOT)
unnamed: R7.1, R8.2, U11.5 (EN)
unnamed: C13.2, R10.1, R11.2, U11.4 (FB)
unnamed: C10.2, L2.1, U11.2 (SW)
PA0: J19.1, U4.14 (PA0)
PB2: J20.1, U4.28 (PB2)
PB4: J21.1, U4.56 (PB4)
PB5: J22.1, U4.57 (PB5)
PB7: J23.1, U4.59 (PB7)
PC5: J13.1, U4.25 (PC5)
PC8: J14.1, U4.39 (PC8)
PC9: J15.1, U4.40 (PC9)
PC13: J16.1, U4.2 (PC13)
PC14: J17.1, U4.3 (PC14)
PC15: J18.1, U4.4 (PC15)
PD2: J12.1, U4.54 (PD2)
PIN_B-: Q2.3 (D)
RX1: J8.2, U4.43 (PA10)
RX2: J25.2, U4.17 (PA3)
RX3: J27.2, U4.30 (PB11)
RX6: J28.2, U4.38 (PC7)
SCLK_GYRO: U4.51 (PC10), U6.23 (SCL/SCLK)
SWCLK: J33.1, U4.49 (PA14)
SWDIO: J32.1, U4.46 (PA13)
TX1: J8.1, U4.42 (PA9)
TX2: J25.1, U4.16 (PA2)
TX3: J27.1, U4.29 (PB10)
TX6: J28.1, U4.37 (PC6)
USB_CON_D+: J1.A6 (D+), J1.B6 (D+), U9.3 (I/O2)
USB_CON_D-: J1.A7 (D-), J1.B7 (D-), U9.1 (I/O1)
USB_D+: R20.2, U4.44 (PA11)
USB_D-: R19.2, U4.45 (PA12)
VIDEO_IN: C38.2, J26.1, R22.2
VIDEO_OUT: J31.1, R21.2

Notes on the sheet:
BUZZER
SPL06 BAROMETER
TYPE C CONNECTOR
BEC 9V 2A (VIN: 10V-28V)
STM32F405
VTX
MOUNTING HOLES
LEDS
GROUND
ICM-20948 IMU
Flight Controller F4
UART
REVERSE POLARITY PROTECTION
ST_LINK
FLASH
GPS
POWER
ESC PADS
1.8V REGULATOR
3.3V REGULATOR
POWER DIODE
GPIOs
BEC 5V 3A (VIN: 8V-28V)
BATTERY DETECTION
CAM_INPUT
OSD AT7456E

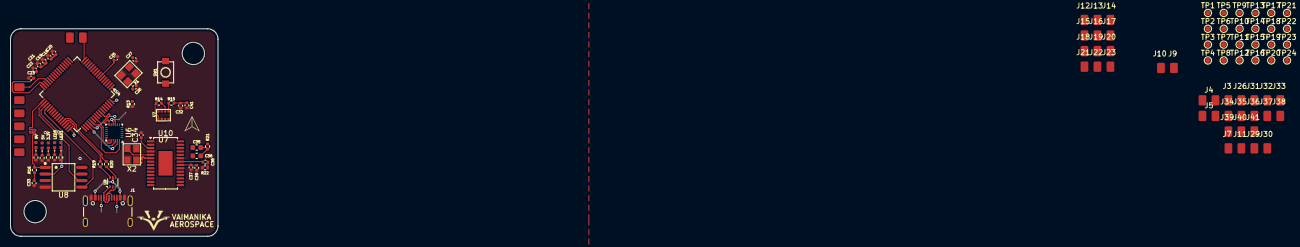
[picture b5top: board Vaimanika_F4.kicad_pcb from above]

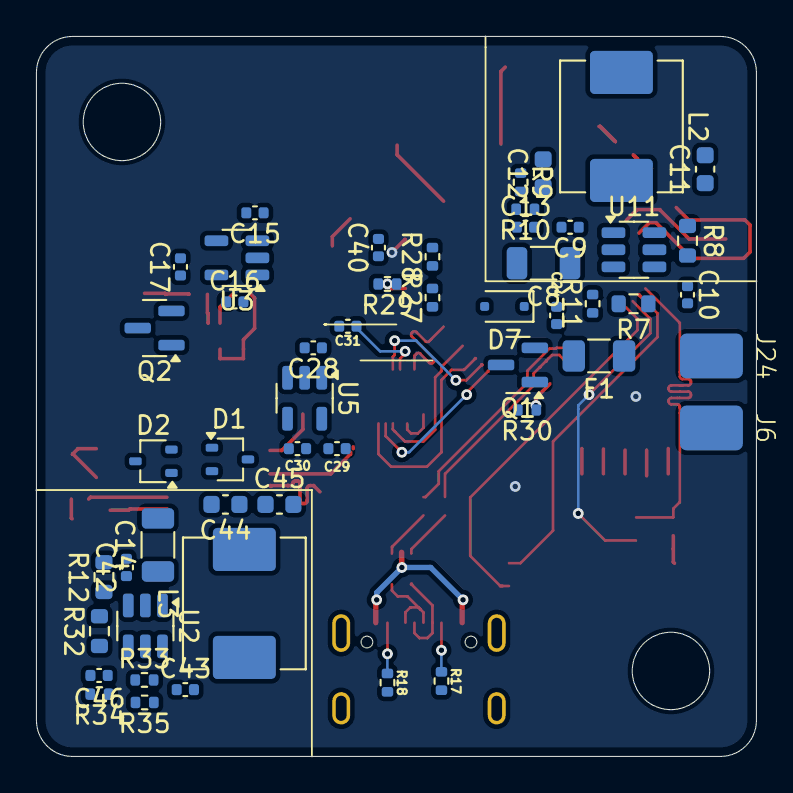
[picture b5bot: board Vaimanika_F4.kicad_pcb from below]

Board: 4 copper layers, 40.0 x 40.0 mm, 162 parts (51 on the bottom side), 100 nets.

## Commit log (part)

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2026-03-12 Initial commit - KiCAD aerospace projects
2026-03-12 12-03-2026-02nd
2026-03-12 12-03-2026-03rd
2026-03-28 28-03-2025
2026-04-10 10-04-2026
2026-04-15 15-04-2026
2026-04-23 23-04-2026
2026-04-24 24-04-2026
2026-04-28 28-04-2026
2026-04-29 29-04-2026
2026-05-01 01-05-2026
2026-05-02 02-05-2026
2026-05-05 05-05-2026
2026-05-12 12-05-2026
2026-05-14 14-05-2026
2026-05-18 18-05-2026
2026-05-20 20-05-2026
2026-05-21 21-05-2026
2026-05-22 22-05-2026
2026-05-25 25-05-2026
2026-05-26 26-05-2026
2026-05-27 27-05-2026
2026-05-28 28-05-2026
2026-05-29 29-05-2026//WFH due to heavy rain
2026-05-30 30-05-2026//WFO
2026-06-01 02-06-2026//WFO
2026-06-03 Pilot PCB Done/03-06-2026
2026-06-04 Pilot PCB Done/04-06-2026
